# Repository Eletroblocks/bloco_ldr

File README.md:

# ldr
Varia a RESISTÊNCIA conforme a LUZ que incide sobre ele, controlando a energia que passa para os blocos seguintes.

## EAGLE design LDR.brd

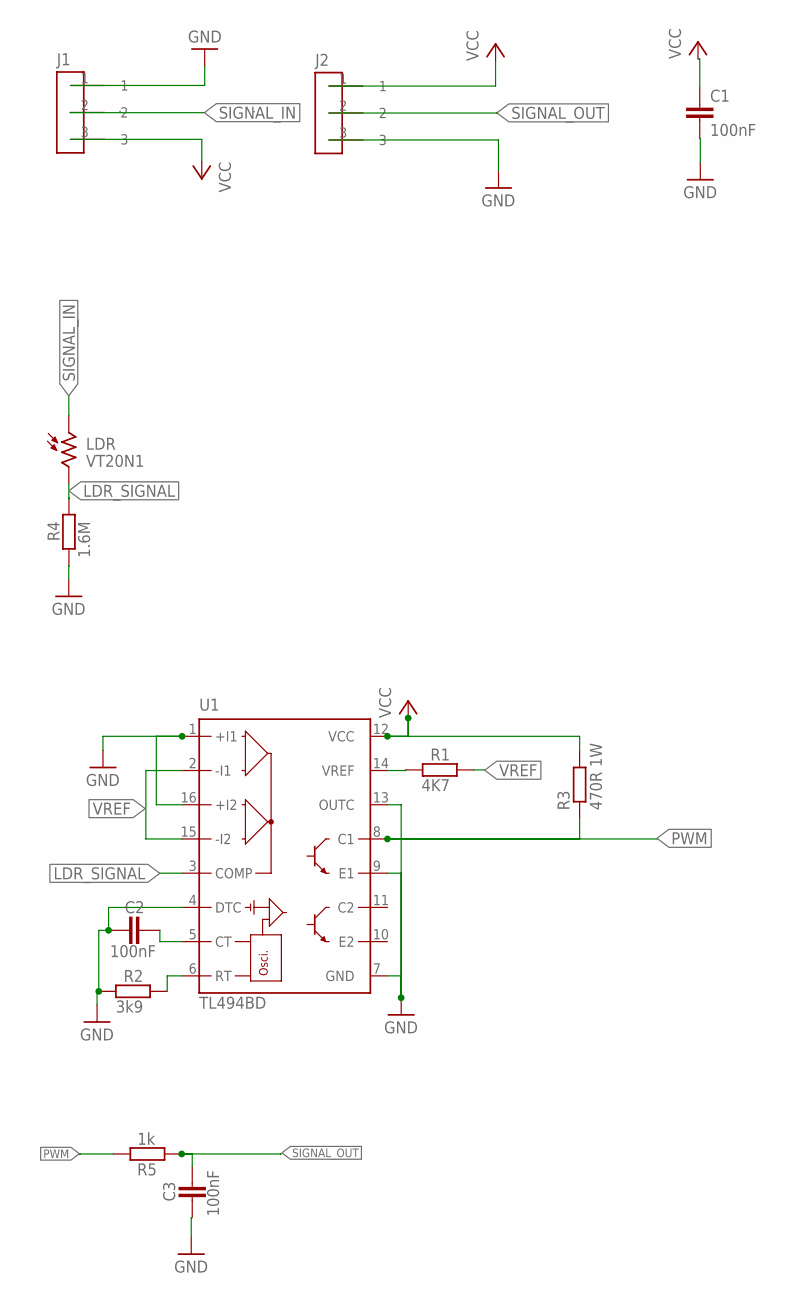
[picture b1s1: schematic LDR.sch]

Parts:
C1, C2, C3: 100nF; C0805
J1: CONECTOR_MACHO; MALE
J2: CONECTOR_FEMEA; FEMALE
LDR: VT20N1; TO46-VT200
R1: 4K7; R0805W
R2: 3k9; R0805W
R3: 470R 1W; R2512
R4: 1.6M; R0805W
R5: 1k; R0805W
U1: TL494BD; SO16

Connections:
GND: C1.2, C2.1, C3.1, J1.1, J2.3, R2.2, R4.2, U1.1 (+I1), U1.4 (DTC), U1.7 (GND), U1.9 (E1), U1.13 (OUTC), U1.16 (+I2)
LDR_SIGNAL: LDR.2, R4.1, U1.3 (COMP)
unnamed: C2.2, U1.5 (CT)
unnamed: R1.2, U1.14 (VREF)
unnamed: R2.1, U1.6 (RT)
PWM: R3.1, R5.1, U1.8 (C1)
SIGNAL_IN: J1.2, LDR.1
SIGNAL_OUT: C3.2, J2.2, R5.2
VCC: C1.1, J1.3, J2.1, R3.2, U1.12 (VCC)
VREF: R1.1, U1.2 (-I1), U1.15 (-I2)

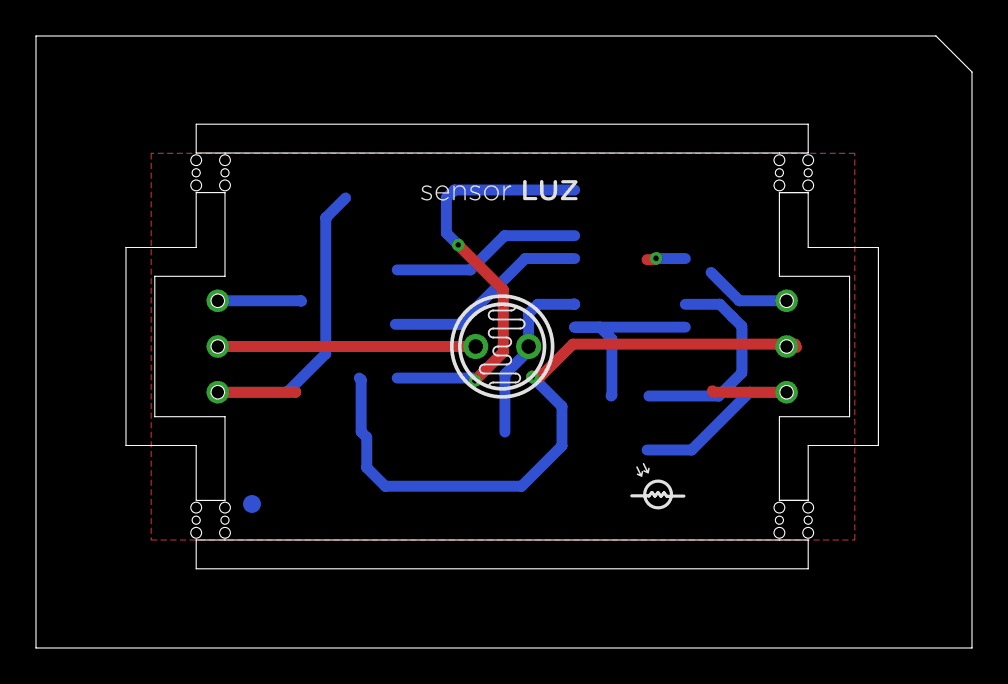
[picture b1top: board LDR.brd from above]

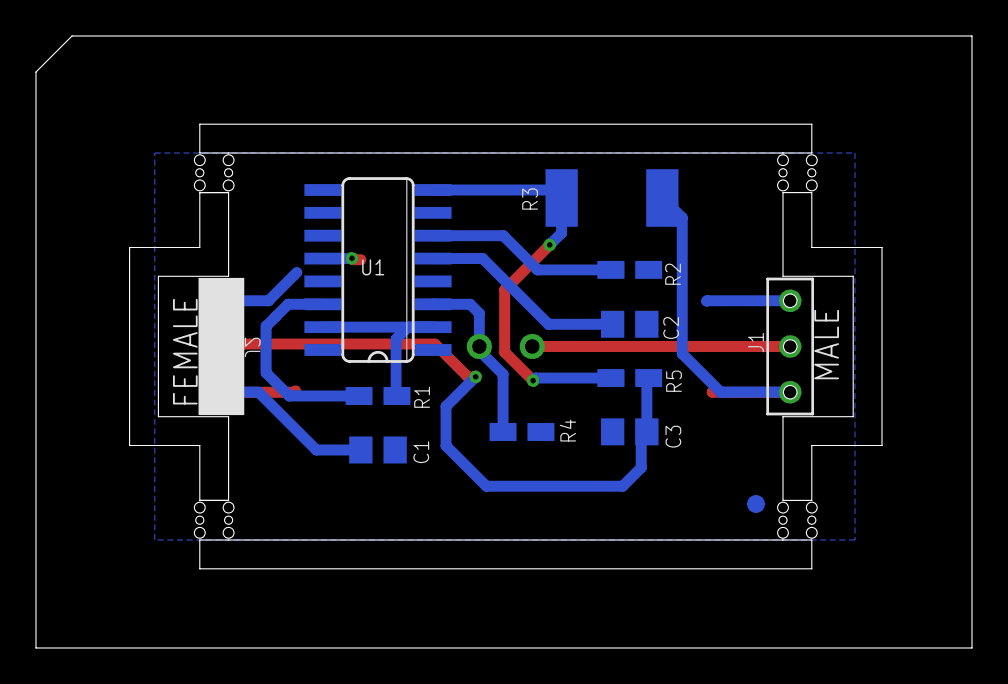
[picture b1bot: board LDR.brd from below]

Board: 2 copper layers, 52.0 x 34.0 mm, 17 parts (10 on the bottom side), 10 nets.

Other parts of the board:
U$1: FIDUCIAL_G10
U$2, U$3, U$4, U$5: STAMP_DUPLO

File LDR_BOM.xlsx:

BOM LIST LDR
DESCRIPTION | QUANTITY | POSITION | PART NUMBER
RESISTOR 4.7K 0805 | 1 | R1 | CRCW08054K70FKEAC, can be replaced to similar
RESISTOR 3.9K 0805 | 1 | R2 | CR0805-JW-392ELF, can be replaced to similar
RESISTOR 470R. 2512 | 1 | R3 | RC2512FK-07470RL, can be replaced to similar
RESISTOR 1.6M 0805 | 1 | R4 | CRCW08051M60FKEA, can be replaced to similar
CAPACITOR 100nF 0805 | 2 | C1,C2 | UMF212B7104KGHT, can be replaced to similar
LDR | 1 | LDR | GL5528, can be replaced to similar
TL494 | 1 | U1 | TL494CNSRG4
MALE CONNECTOR | 1 | J1 | THIS COMPONENT IS PROVIDE BY ELETROBLOCKS
FEMALE CONNECTOR | 1 | J2 | THIS COMPONENT IS PROVIDE BY ELETROBLOCKS

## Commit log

2020-11-23 init project
2020-11-23 correção de pads, adição de label para versionamento e plano de VCC
2020-11-23 adição de filtro no SIGNAL_OUT para correção do Duty Cycle
2020-11-23 correção de label
2020-12-28 organizando arquivos
2020-12-28 imagem
2021-03-11 V1.1.1

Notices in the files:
parts and their libraries:
dicons: Copyright (C) 2004, Bob Starr (rtzaudio@mindspring.com)
